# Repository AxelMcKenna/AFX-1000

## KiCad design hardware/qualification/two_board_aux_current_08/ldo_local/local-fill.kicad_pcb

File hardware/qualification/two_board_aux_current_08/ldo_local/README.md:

# Isolated main-LDO local bypass

Final candidate: `inputs-local-return-08/power_protection.kicad_pcb`. Its complete materialized schematic, footprint libraries and project context are frozen under this unique run directory and bound by `inputs-local-return-08.json`. This is not selected TBP73 and does not complete IN/EN source delivery or the held-rail design.

P_C907 is KEMET C0603C105K3RACTU, nominal 1 µF / 25 V X7R / 10%, at (187.5,126.6), F.Cu, 180°. Its positive pad connects to P_U102.8 through 0.809217 mm of 0.3 mm trace; its ground pad connects directly to P_U102.9 through 3.383580 mm of 0.4 mm trace. Four surface tracks, no vias, no existing part moved. The earlier 2.779 mm lead followed by 13.019 mm of existing ground chain is rejected as a short local bypass path.

The In1 main-ground patch is the explicit rectangle (186.7,127.8)–(188.0,130.8), 3.9 mm². Native fill contact is anchored to two original main-ground zones with 16 and four source-connected contacts respectively. All original native groups, quiet objects, copper and 55 full-identity anonymous pad mappings are preserved except the declared two new capacitor joins; opens remain 1,943. All original pads/tracks retain their reference copper, and new copper and conservative new pad rectangles clear both mechanical keepout sets.

The F.Cu AGND cutback is explicitly local, not a clearance waiver: source zone `d0572a8e-b95d-5c59-9a7c-1d3514a507b4`, first native corner-run replace 118:138 with 118:132. It removes 0.744739497 mm² within (187.69,125.95)–(188.57,127.65), adds none, preserves every old ground contact and leaves the other 48 source zones exact. Its thin native peninsula next to an old DC_IN antipad extends beyond a simple pad-clearance offset; the exact saved native corner-run and bounded rectangle are the review authority. Remote refill runs and the extra native polygon are rejected. Clearance rules are unchanged.

The selected-zone native interface loads/checks the whole board, builds connectivity, fills only the new zone, then imports only that fill. `failure-provenance.json` retains the prior 180 s full-board CLI timeout and the successful 2.16 s changed-workload diagnostic. The timeout's internal cause is not established. No unchanged failed operation was retried. `native-07` additionally had a new reference-text overlap; the final candidate changes only C907 reference size/position and checks exact board AST equality otherwise.

Schematic UUID and footprint identity are checked separately from net parity, including all 1,105 electrical parts and C907. Native command completion alone never passes the gate: the host manifest must match every native input byte, and recorded process hashes must match expected host hashes even when `inputs_unchanged` is true. This addresses the rejected `native-06` reused-path discrepancy without modifying a shared runner.

Qualification remains conditional. TI's hard input-capacitance minimum is effective 0.1 µF; the long-source 10 µF recommendation is not satisfied by assuming nominal 1 µF. The cached KEMET primary PDF page 2 bias curves are typical simulations, explicitly not specifications on page 4. Actual effective capacitance over voltage/temperature/age, the 39.247 mm input feed and existing remote C102 transient behavior, installed current/thermal performance, IN/EN routing and the wider reset/held-distribution gates remain open. Maximum capacitor body height is 0.95 mm; housing integration has not been qualified. Four TPS3703 DSE 0.15 mm clearances remain unwaived against the 0.20 mm rule.

Run the verifier and ten mutation tests:

```
.venv/bin/python -m hardware.qualification.two_board_aux_current_08.ldo_local.verify
.venv/bin/python -m unittest hardware.qualification.two_board_aux_current_08.ldo_local.test_verify
```

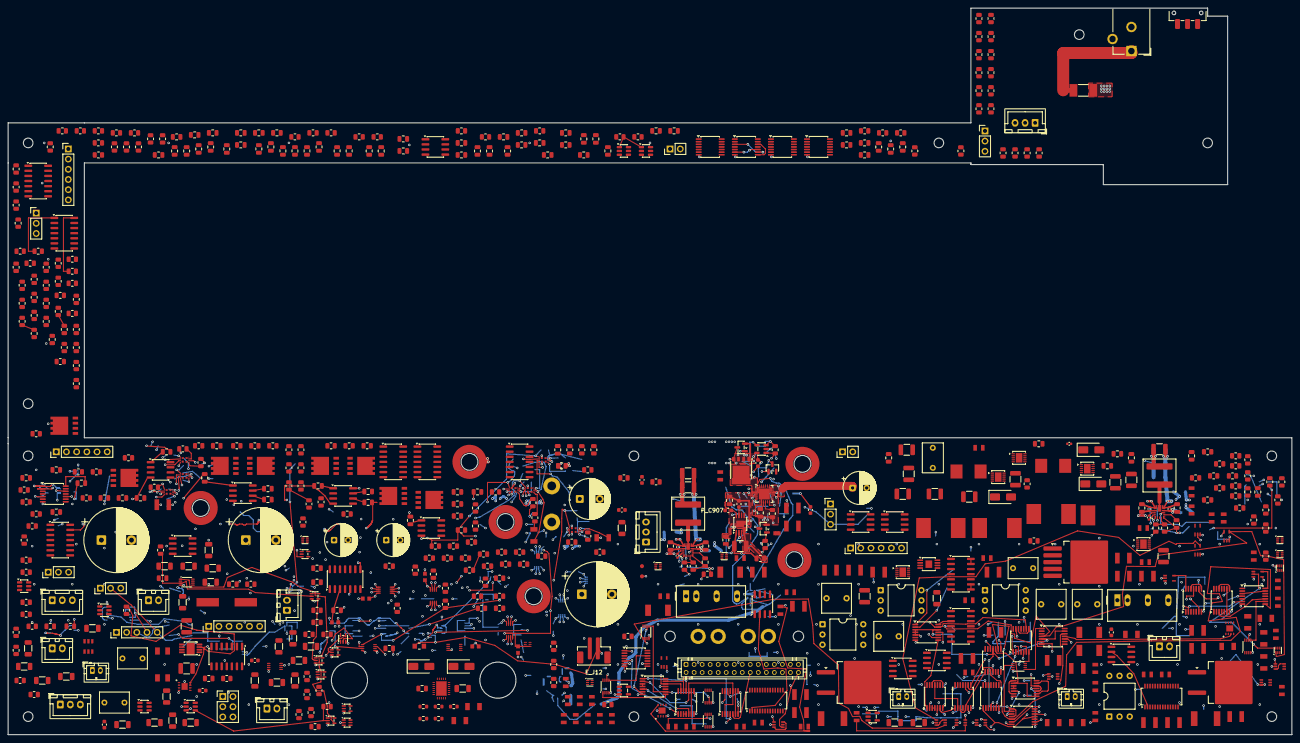
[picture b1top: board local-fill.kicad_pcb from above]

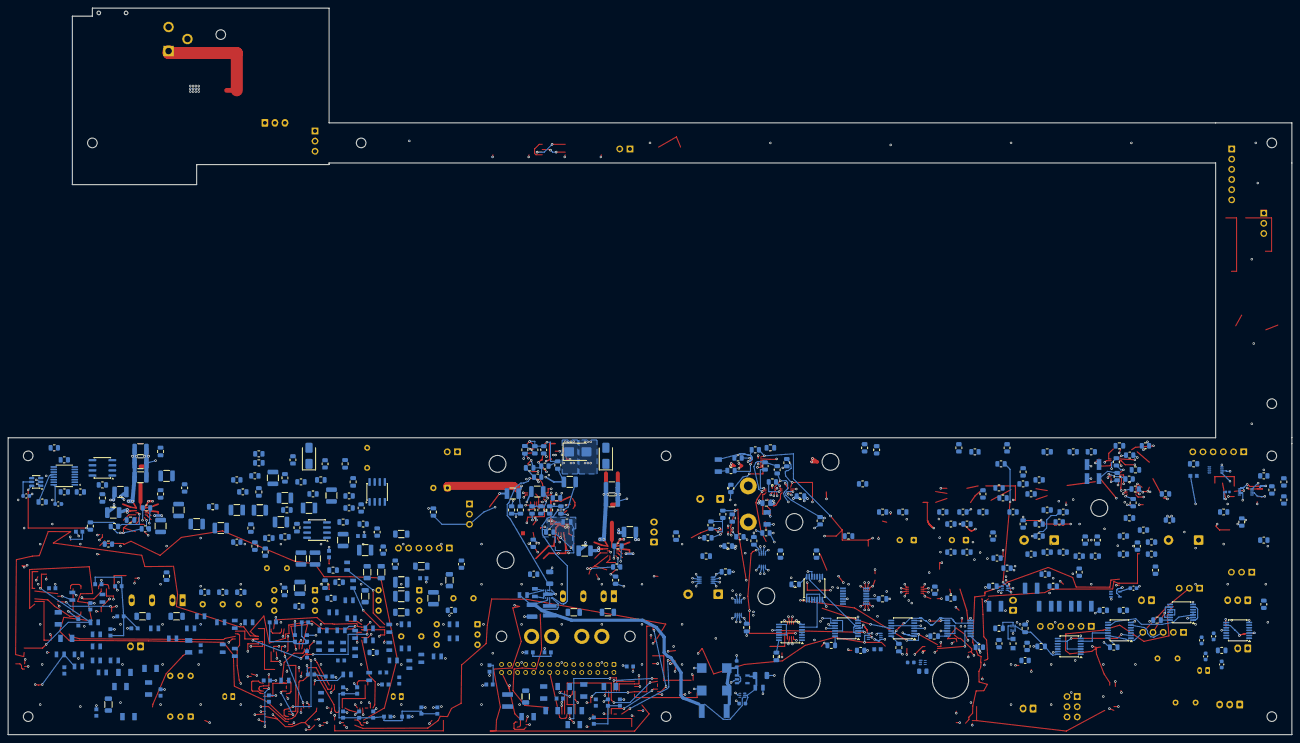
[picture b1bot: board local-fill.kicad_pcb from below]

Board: 8 copper layers, 320.0 x 181.1 mm, 1120 parts (428 on the bottom side), 643 nets.

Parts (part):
E_C1, E_C5, E_C17, E_C21, E_C25, E_C34, E_C35, E_C37, E_C57, E_C58, E_C59, E_C66, E_C67, E_C68, E_C69, E_C70, E_C71, E_C72, E_C73, E_C74, E_C75, E_C76, E_C77: 100nF 16V X7R; C_0805_2012Metric
E_C2, E_C3, E_C6, E_C7, E_C10, E_C11, E_C14, E_C15: 10pF 100V C0G 5%; C_0805_2012Metric
E_C4, E_C8: 1500uF 35V electrolytic 20% EEUFR1V152S; CP_Radial_D16.0mm_P7.50mm
E_C9, E_C13, E_C29, E_C36: 100nF 50V X7R 10%; C_0805_2012Metric
E_C12, E_C16: 220uF 35V electrolytic 20% EEUFR1V221; CP_Radial_D8.0mm_P3.50mm
E_C20: 1500uF 16V electrolytic 20% EEUFR1C152; CP_Radial_D10.0mm_P5.00mm
E_C24: 4700uF 16V electrolytic 20% EEUFR1C472; CP_Radial_D16.0mm_P7.50mm
E_C26: 1uF 16V X7R; C_0805_2012Metric
E_C27, E_C28, E_C30, E_C31, E_C32, E_C33, E_C53, E_C54, E_C55, E_C56: 100pF 50V C0G 5%; C_0805_2012Metric
E_C38: 10uF 16V X7R; C_0805_2012Metric
E_C39, E_C41, E_C49, E_C61, E_C62, E_C63, E_C64, E_C65: 100nF 50V C0G 5% C1210C104J5GACTU; KEMET_C1210_LevelB
E_C40, E_C42, E_C44, E_C46, E_C48, E_C50, E_C52: 1uF 50V X7R; C_0805_2012Metric
E_C43, E_C45, E_C47, E_C51: 47nF 50V C0G 5% C1206C473J5GACTU; KEMET_C1206_LevelB
E_C60: 10nF 50V C0G 5%; C_0805_2012Metric
E_C78, E_C80, E_C81, E_C82, E_C83, E_C84, E_C85: 100nF 16V X7R 10% KEMET C0603C104K4RACTU; KEMET_C0603_LevelB
E_C79: 100nF 16V X7R 10% KEMET C0402C104K4RACTU; KEMET_C0402_LevelB
E_C86: 100nF 50V X7R C0603C104K5RACTU; AX03_C0603
E_C900: 100nF 50V X7R 10%; TB05_P_Capacitor_SMD__C_0603_1608Metric
E_J1, E_J3: Header6; PinHeader_1x06_P2.54mm_Vertical
E_J4: Alpha3079_AWG14_DIG_FORCE; AWG14_Force_2x1_P9mm_Engineering
E_J5, E_J6: Header3; PinHeader_1x03_P2.54mm_Vertical
E_J7, E_J8, E_J10, E_J11: 7466003R; 7466003R_M3_SMT_Annulus_NPTH
E_J9: E28 CONTROL; PinHeader_1x05_P2.54mm_Vertical
E_J12: JST B2B-PH-SM4-TB(LF)(SN); JST_B2B_PH_SM4_TB_MechanicalLands
E_Q1, E_Q2, E_Q3, E_Q4, E_Q5, E_Q6, E_Q7, E_Q8: CSD18540Q5B; CSD18540Q5B_TI_Q5B
E_R1, E_R9, E_R17, E_R25: 22 1%; R_0805_2012Metric
E_R2, E_R10, E_R18, E_R26, E_R60, E_R63, E_R68, E_R71, E_R76, E_R81, E_R86, E_R91: 20M 1%; R_0805_2012Metric
E_R3, E_R5, E_R11, E_R13, E_R19, E_R21, E_R27, E_R29, E_R61, E_R64, E_R69, E_R72, E_R77, E_R82, E_R87, E_R92: 10k 1%; R_0805_2012Metric
E_R4, E_R12, E_R20, E_R28, E_R98, E_R102, E_R106, E_R110, E_R114, E_R118, E_R122: 100 1%; R_0805_2012Metric
E_R6, E_R7, E_R14, E_R15, E_R22, E_R23, E_R30, E_R31: 15k 1%; R_0805_2012Metric
E_R8, E_R16, E_R24, E_R32, E_R40, E_R48: 47k 1%; R_0805_2012Metric
E_R49: 150k 0.01% 5ppm; R_0805_2012Metric
E_R50: 6.2k 0.01% 5ppm; R_0805_2012Metric
E_R51, E_R54, E_R58, E_R59, E_R62, E_R66, E_R67, E_R70, E_R74, E_R75, E_R79, E_R80, E_R85, E_R90, E_R94, E_R124, E_R127, E_R130, E_R133: 10k 0.01% 5ppm; R_0805_2012Metric
E_R52, E_R55: 1k 1%; R_0805_2012Metric
E_R53: 100k 0.01% 5ppm; R_0805_2012Metric
E_R56: 143k 0.01% 5ppm; R_0805_2012Metric
E_R57: 3.3k 0.01% 5ppm; R_0805_2012Metric
E_R65: 90.9k 0.01% 5ppm; R_0805_2012Metric
E_R73, E_R78: 31.6k 0.01% 5ppm; R_0805_2012Metric
E_R83: 10.7k 0.01% 5ppm; R_0805_2012Metric
E_R84: 5.76k 0.01% 5ppm; R_0805_2012Metric
E_R88: 16.2k 0.01% 5ppm; R_0805_2012Metric
E_R89: 13.3k 0.01% 5ppm; R_0805_2012Metric
E_R93: 200k 0.1% ERA6AEB204V - COMPLETE1% RECEIVING; R_0805_2012Metric
E_R95, E_R99, E_R103, E_R107, E_R111, E_R115, E_R119, E_R125, E_R128, E_R131, E_R134, E_R136, E_R141: 10k; R_0805_2012Metric
E_R96, E_R100, E_R104, E_R108, E_R112, E_R116, E_R120, E_R140: 47k; R_0805_2012Metric
E_R97, E_R101, E_R117: 2.43k 0.1%; R_0805_2012Metric
E_R105, E_R109, E_R113, E_R121: 604 0.1%; R_0805_2012Metric
E_R123, E_R126, E_R129, E_R132: 28.7k 0.01% 5ppm; R_0805_2012Metric
E_R135: 10k 0.1% 25ppm Panasonic ERA6AEB103V; Resistor_SMD_Panasonic_ERA6A_2012
E_R137: 11.1k 0.1%; R_0805_2012Metric
E_R138: 39.2 0.1%; R_0805_2012Metric
E_R139: 10k 0.1%; R_0805_2012Metric
E_R142: 15k; R_0805_2012Metric
E_R143: 15k 0.1% 25ppm Panasonic ERA6AEB153V; Resistor_SMD_Panasonic_ERA6A_2012
E_R900: 10k 0.1% 25ppm; TB05_E_Resistor_SMD__R_0805_2012Metric
E_U1, E_U2, E_U3, E_U4: SI8751AB-ISR; SOIC-8_3.9x4.9mm_P1.27mm
E_U7: REF35125QDBVR; SOT-23-6
E_U8: OPA2333AID; SOIC-8_3.9x4.9mm_P1.27mm
E_U9, E_U10: TLV1824DR; SOIC-14_3.9x8.7mm_P1.27mm
E_U11, E_U12, E_U24, E_U25, E_U26, E_U27: SN74LVC08APWR; TSSOP-14_4.4x5mm_P0.65mm
E_U13, E_U14, E_U15, E_U16, E_U17, E_U32, E_U33: TPS259482LYWP; TPS259482L_YWP0012A
E_U18: TLV1824PWR; TLV1824_PW0014A
E_U19, E_U20: TPS389001DSET; TPS389001_DSE0006A
E_U21, E_U22: SN74LVC02APWR; TSSOP-14_4.4x5mm_P0.65mm
E_U23: SN74LVC32APWR; TSSOP-14_4.4x5mm_P0.65mm
E_U28: SN74LVC14APWR; SN74LVC14A_PW0014A
E_U29, E_U30, E_U31, E_U34: SN74AUP2G08DCUR; SN74AUP2G08_DCU0008A
E_U35, E_U36, E_U37, E_U38, E_U39, E_U40, E_U41: SN74AUP3G17DCUR; SN74LVC3G17_DCU0008A
E_U42: SN74LVC3G17DCUR; SN74LVC3G17_DCU0008A
E_U43: SN74AUP1G17DCKR; AX03_DCK0005A
E_U900: TPS3703A5330DSER; AUX_READY__TI_DSE0006A
F_C1, F_C2: 10uF 25V C3225X7R1E106K250AC; Capacitor_SMD__C_1210_3225Metric
F_C3, F_C14, F_C22, F_C23: 10nF 50V C0G C1206C103J5GACTU; Capacitor_SMD__C_1206_3216Metric
F_C4, F_C5, F_C6, F_C8, F_C9, F_C10, F_C11, F_C12, F_C13, F_C15, F_C16, F_C17, F_C18, F_C19, F_C24: 100nF 25V C0G C1206C104J3GACTU; Capacitor_SMD__C_1206_3216Metric
F_C7: 2.7nF 50V C0G5% C0603C272J5GACTU; Capacitor_SMD__C_0603_1608Metric
F_C20, F_C21: 15pF 50V C0G5% C0603C150J5GACTU; Capacitor_SMD__C_0603_1608Metric
F_C201, F_C202, F_C301, F_C302: 100nF25V C0G5% C1206C104J3GACTU; Capacitor_SMD__C_1206_3216Metric
F_C203, F_C303: 1uF63V10% WIMA MKS2C041001F00KSSD; Capacitor_THT__C_Rect_L7.2mm_W5.0mm_P5.00mm
F_C401, F_C402, F_C403, F_C404: 100nF50V X7R10% C0603C104K5RACTU - EFFECTIVE60nF_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; Capacitor_SMD__C_0603_1608Metric
F_J2, F_J3, F_J4, F_J201: JST B2B-XH-A / XHP-2 / SXH-001T-P0.6; Connector_JST__JST_XH_B2B-XH-A_1x02_P2.50mm_Vertical
F_J5: AVRISP2x3 target-powered3.3V sense ONLY; Connector_PinHeader_2.54mm__PinHeader_2x03_P2.54mm_Vertical
F_J202, F_J203: JST B3B-XH-A / XHP-3 / SXH-001T-P0.6; Connector_JST__JST_XH_B3B-XH-A_1x03_P2.50mm_Vertical
F_J401: JST B2B-PH-K-S / PHR-2 / SPH-002T-P0.5S; Connector_JST__JST_PH_B2B-PH-K_1x02_P2.00mm_Vertical
F_R1, F_R16, F_R17, F_R21, F_R23: 1k 0.1%25ppm TNPW08051K00BEEA; Resistor_SMD__R_0805_2012Metric
F_R2, F_R6, F_R10, F_R13, F_R202, F_R302: 10k 0.1%25ppm TNPW080510K0BEEA; Resistor_SMD__R_0805_2012Metric
F_R3, F_R4, F_R5, F_R7, F_R14, F_R15: 47k 0.1%25ppm TNPW080547K0BEEA; Resistor_SMD__R_0805_2012Metric
F_R8: 68k 0.1%25ppm TNPW080568K0BEEA; Resistor_SMD__R_0805_2012Metric
F_R9: 39k 0.1%25ppm TNPW080539K0BEEA; Resistor_SMD__R_0805_2012Metric
F_R11: 56.2k 0.1%25ppm TNPW080556K2BEEA; Resistor_SMD__R_0805_2012Metric
F_R12, F_R24, F_R201, F_R203, F_R301, F_R303: 100k 0.1%25ppm TNPW0805100KBEEA; Resistor_SMD__R_0805_2012Metric
F_R20, F_R22: 20k 0.1%25ppm TNPW080520K0BEEA; Resistor_SMD__R_0805_2012Metric
F_R401: 220k 0.1%25ppm TNPW0805220KBEEA - COMPLETE1% RECE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; Resistor_SMD__R_0805_2012Metric
F_U1: ATtiny84A-SSUR; Package_SO__SOIC-14_3.9x8.7mm_P1.27mm
F_U2: TPS7A1633DGNR; TI_DGN0008C
F_U3: SN74LVC2G17DCKR; Package_TO_SOT_SMD__SOT-363_SC-70-6
F_U4: TPS3431SDRBR; TI_DRB0008A_TPS3431
F_U5: SN74AUP1G17DCKR; Package_TO_SOT_SMD__SOT-353_SC-70-5
F_U6: SN74LVC1T45DBVR; Package_TO_SOT_SMD__SOT-23-6
F_U7: SN74LVC1G14DCKR; Package_TO_SOT_SMD__SOT-353_SC-70-5
F_U8: SN74LVC1G74DCUR; TI_DCU0008A
F_U9: TPS389001DSET; Package_SON__WSON-6_1.5x1.5mm_P0.5mm
F_U10, F_U11: SN74LVC1G17DCKR; Package_TO_SOT_SMD__SOT-353_SC-70-5
F_U12, F_U13: SN74LVC1G08DCKR; Package_TO_SOT_SMD__SOT-353_SC-70-5
F_U14: SN74LVC1G06DCKR; Package_TO_SOT_SMD__SOT-353_SC-70-5
F_U15: TLP175A(TPL,E); RMX_FH02__TLP175A_11-4M1S_Receiving
F_U16: SN74LVC1G34DCKR; Package_TO_SOT_SMD__SOT-353_SC-70-5
F_U201, F_U301: TPS2553DBVR-1; Package_TO_SOT_SMD__SOT-23-6
F_U401: TPS2553DBVR-1; TI_DBV0006A
F_X1: ABLS-4.000MHZ-12-D4Y-T; RMX_FH02__ABLS_Manufacturer_Land
G_C1: 1uF 50V X7R 10%; C_0805_2012Metric
G_C2: 2.2uF 50V X7R 10%; C_1206_3216Metric
G_C3, G_C4: 100nF25V C0G C1206C104J3GACTU; PROPOSED_KEMET1206_LevelB
G_D1: SMAJ15A-E3/61; D_SMA
G_D2: SS14-E3/61T; D_SMA
G_NT1: MODULE_RETURN_STAR; Return_Star
G_R1, G_R3: 470k 0.1% 25ppm; R_0603_1608Metric
G_R2: 59.0k 0.1% 25ppm; R_0603_1608Metric
G_R4: 43.2k 0.1% 25ppm; R_0603_1608Metric
G_R5: 22.1k 0.1% 25ppm; R_0603_1608Metric
G_U1: TPS26601RHFR; TI_RHF0024A
H_NEW1: PROPOSED_NPTH; H_NEW1
H_NEW2: PROPOSED_NPTH; H_NEW2
H_NEW3: PROPOSED_NPTH; H_NEW3
H_NEW4: PROPOSED_NPTH; H_NEW4
H_NEW5: PROPOSED_NPTH; H_NEW5
H_NEW6: PROPOSED_NPTH; H_NEW6
H_NEW7: PROPOSED_NPTH; H_NEW7
H_NEW8: PROPOSED_NPTH; H_NEW8
H_NEW9: PROPOSED_NPTH; H_NEW9
H_NEW10: PROPOSED_NPTH; H_NEW10
H_NEW11: PROPOSED_NPTH; H_NEW11
H_TOUCH1: PROPOSED_NPTH; H_TOUCH1
H_TOUCH2: PROPOSED_NPTH; H_TOUCH2
I_F1: 045106.3MRL 6.3A 125V; Fuse_Littelfuse-NANO2-451_453
I_J1: PJ-102AH; PJ102AH_RearEdge_E23
I_J3: B3B-XH-A(LF)(SN); JST_XH_B3B-XH-A_1x03_P2.50mm_Vertical
I_S1: JS102011SAQN; JS102011SAQN_RearEdge_E23
M_C1, M_C2, M_C3, M_C4, M_C5, M_C6, M_C7, M_C8, M_C9, M_C10, M_C11, M_C12, M_C13, M_C14, M_C15, M_C16, M_C17, M_C18, M_C19, M_C20, M_C21, M_C22, M_C23, M_C24, M_C25, M_C26, M_C27, M_C28, M_C29, M_C30, M_C31, M_C32, M_C33, M_C34, M_C35, M_C36: 100pF C0G 5%; C_0805_2012Metric
M_C37, M_C38, M_C39, M_C40, M_C41, M_C42, M_C43, M_C44, M_C45, M_C46, M_C47, M_C48: 100nF 16V X7R; C_0805_2012Metric
M_C49: 2.2uF 16V X7R; C_0805_2012Metric
M_C50: 10uF 16V X7R; C_0805_2012Metric
M_C51: 1uF 16V X7R; C_0805_2012Metric
M_J1, M_J3: Conn_01x03; PinHeader_1x03_P2.54mm_Vertical
M_J2: Conn_01x06; PinHeader_1x06_P2.54mm_Vertical
M_J4: Conn_01x02; PinHeader_1x02_P2.54mm_Vertical
M_R1, M_R7, M_R25, M_R31: 91k 0.01% 5ppm; R_0805_2012Metric
M_R2, M_R4, M_R8, M_R10, M_R11, M_R14, M_R16, M_R19, M_R21, M_R22, M_R26, M_R28, M_R32, M_R33, M_R35, M_R36, M_R39, M_R41, M_R44, M_R45, M_R47, M_R48, M_R51, M_R53, M_R56, M_R58, M_R59, M_R62, M_R64, M_R67, M_R69, M_R70, M_R73, M_R75, M_R77, M_R80, M_R82, M_R84, M_R85, M_R88, M_R90, M_R92, M_R96, M_R98, M_R99, M_R103, M_R105, M_R106, M_R108, M_R111: 10k 0.01% 5ppm; R_0805_2012Metric
M_R3: 3.57k 0.01% 5ppm; R_0805_2012Metric
M_R5, M_R12, M_R17, M_R23, M_R29, M_R37, M_R42, M_R49, M_R54, M_R60, M_R65, M_R71, M_R78, M_R86, M_R93, M_R100: 20M 1%; R_0805_2012Metric
M_R6, M_R13, M_R18, M_R24, M_R30, M_R38, M_R43, M_R50, M_R55, M_R61, M_R66, M_R72, M_R79, M_R87, M_R94, M_R101, M_R113: 10k 1%; R_0805_2012Metric
M_R9: 3.01k 0.01% 5ppm; R_0805_2012Metric
M_R15: 3.4k 0.01% 5ppm; R_0805_2012Metric
M_R20: 2.87k 0.01% 5ppm; R_0805_2012Metric
M_R27, M_R95: 11.5k 0.01% 5ppm; R_0805_2012Metric
M_R34: 604 0.01% 5ppm; R_0805_2012Metric
M_R40: 11.3k 0.01% 5ppm; R_0805_2012Metric
M_R46: 412 0.01% 5ppm; R_0805_2012Metric
M_R52, M_R63: 8.2k 0.01% 5ppm; R_0805_2012Metric
M_R57, M_R68: 1.78k 0.01% 5ppm; R_0805_2012Metric
M_R74, M_R81, M_R89: 499 0.01% 5ppm; R_0805_2012Metric
M_R76: 374 0.01% 5ppm; R_0805_2012Metric
M_R83: 127 0.01% 5ppm; R_0805_2012Metric
M_R91: 768 0.01% 5ppm; R_0805_2012Metric
M_R97: 270 0.01% 5ppm; R_0805_2012Metric
M_R102, M_R104: 100k 0.01% 5ppm; R_0805_2012Metric
M_R107, M_R109: 80.6k 0.01% 5ppm; R_0805_2012Metric
M_R110: 105k 0.01% 5ppm; R_0805_2012Metric
M_R112: 100k 1%; R_0805_2012Metric
M_R114: 330k 1%; R_0805_2012Metric
M_U1, M_U2, M_U3, M_U4: TLV1824IDR; SOIC-14_3.9x8.7mm_P1.27mm
M_U5: OPA4192ID; SOIC-14_3.9x8.7mm_P1.27mm
M_U6: REF5025EIDR; SOIC-8_3.9x4.9mm_P1.27mm
M_U7: TPS3808G01DBVR; SOT-23-6
M_U8: TPS3808G33DBVR; SOT-23-6
M_U9, M_U10, M_U11, M_U12: SN74LVC08APWR; TSSOP-14_4.4x5mm_P0.65mm
N_C1: 56nF50V C0G5% C1206C563J5GACTU - COMPLETE10% RECE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; PROPOSED_KEMET1206_LevelB
N_C2: 33nF50V C0G5% C1206C333J5GACTU - COMPLETE10% RECE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; PROPOSED_KEMET1206_LevelB
N_C3, N_C12, N_C39, N_C55, N_C56, N_C57, N_C58, N_C59, N_C60, N_C61, N_C62, N_C63, N_C64, N_C65, N_C66, N_C67, N_C68, N_C69, N_C70, N_C71, N_C72, N_C73, N_C74, N_C75, N_C76, N_C77, N_C78, N_C79, N_C80, N_C81, N_C82, N_C83, N_C84, N_C85, N_C86, N_C87, N_C88: 100nF 50V X7R10% C0603C104K5RACTU - bypass effect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; PROPOSED_KEMET0603_LevelB
N_C4, N_C31: 10uF 25V X7R MODULE INPUT FILTER/EFFECTIVE/INRUSH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; Capacitor_SMD__C_1206_3216Metric
N_C5, N_C32: 1uF 50V X7R MODULE OUTPUT FILTER/EFFECTIVE HOLD; Capacitor_SMD__C_1206_3216Metric
N_C6, N_C33: 1uF 25V X7R LTC4261 local VIN effective HOLD; Capacitor_SMD__C_1206_3216Metric
N_C7, N_C9, N_C11, N_C13, N_C34, N_C36, N_C38, N_C40: 100nF 25V C0G C1206C104J3GACTU; PROPOSED_KEMET1206_LevelB
N_C8, N_C10, N_C35, N_C37: 10nF 50V C0G COMPLETE10% TIMING RECEIVING; PROPOSED_KEMET1206_LevelB
N_C14, N_C15, N_C16, N_C17, N_C18, N_C19, N_C20, N_C21, N_C22, N_C23, N_C24, N_C25, N_C41, N_C42, N_C43, N_C44, N_C45, N_C46, N_C47, N_C48, N_C49: 100nF 50V C0G C1210C104J5GACTU - COMPLETE10% RAMP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; PROPOSED_KEMET1210_LevelB
N_C26, N_C27, N_C50, N_C51: 2.2uF 63V PET5% MKS2C042201K00JSSD - COMPLETE10% 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; Capacitor_THT__C_Rect_L7.2mm_W7.2mm_P5.00mm_FKS2_FKP2_MKS2_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
N_C28, N_C30, N_C52, N_C54: 47nF 50V C0G C1206C473J5GACTU; PROPOSED_KEMET1206_LevelB
N_C29, N_C53: 100nF 50V C0G C1210C104J5GACTU; PROPOSED_KEMET1210_LevelB
N_C89, N_C90, N_C91, N_C93, N_C94, N_C96: 100nF50V X7R10% C0603C104K5RACTU - EFFECTIVE/PDN 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; PROPOSED_KEMET0603_LevelB
N_C92, N_C95: 47nF50V C0G5% C1206C473J5GACTU - COMPLETE6% RECEI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; PROPOSED_KEMET1206_LevelB
N_C97, N_C98: 100nF25V C0G5% C1206C104J3GACTU - COMPLETE6% CT /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; PROPOSED_KEMET1206_LevelB
N_C99: 100nF25V C0G5% C1206C104J3GACTU - COMPLETE6% UVRE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; PROPOSED_KEMET1206_LevelB
N_C100: 100nF50V X7R10% C0603C104K5RACTU - LOCAL_BYPASS_E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; PROPOSED_KEMET0603_LevelB
N_H101, N_H102: STRAIN_POST_2p6_NPTH_RECEIVING
N_J1: NEW NF03C CONTROL/KELVIN INTERFACE - physical con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; NC265_JST_PHD_B30B-PHDSS_2x15_P2.00mm_Vertical
N_J2: N19 NEW FORCE IN/OUT - connector and harness unse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; NC265_NC265_Force2_18AWG_P5_Drill2p2_Land3p8
N_J3: N19 E28 BANK GATE/COMMON CLAMP - physical interfa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; NC265_JST_PH_B2B-PH-K_1x02_P2.00mm_Vertical
N_J4: N12 NEW FORCE IN/OUT - connector and harness unse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; NC265_NC265_Force2_18AWG_P5_Drill2p2_Land3p8
N_J5: N12 E28 BANK GATE/COMMON CLAMP - physical interfa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; NC265_JST_PH_B2B-PH-K_1x02_P2.00mm_Vertical
N_J6: NEW MODULE INPUT ONLY - keyed JST XH2 receiving c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; NC265_JST_XH_B2B-XH-A_1x02_P2.50mm_Vertical
N_Q1, N_Q2: CSD19536KTT; Package_TO_SOT_SMD__TO-263-2
N_R1, N_R2, N_R8, N_R9: 10k; PROPOSED_TNPW0805_IPC28950
N_R3, N_R10: 205000ohm 0.1% TNPW0805205KBEEA - COMPLETE3% RECE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; PROPOSED_TNPW0805_IPC28950
N_R4, N_R11: 499ohm 0.1% TNPW0805499RBEEA - COMPLETE3% RECEIVI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; PROPOSED_TNPW0805_IPC28950
N_R5, N_R12, N_R95, N_R98, N_R99: 10000ohm 0.1% TNPW080510K0BEEA - COMPLETE3% RECEI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; PROPOSED_TNPW0805_IPC28950
N_R6, N_R7, N_R13, N_R14: 220ohm COMPLETE +/-3% RECEIVING; PROPOSED_TNPW0805_IPC28950
N_R15, N_R16, N_R17, N_R18, N_R19, N_R20, N_R21, N_R22: 47k 3% TOTAL RECEIVING; PROPOSED_TNPW0805_IPC28950
N_R23: 160000ohm COMPLETE0.1% RECEIVING; PROPOSED_TNPU0805_IPC28950
N_R24, N_R41, N_R63, N_R65, N_R80, N_R82: 10k COMPLETE0.1% RECEIVING; PROPOSED_TNPU0805_IPC28950
N_R25, N_R49: 8660ohm COMPLETE0.1% RECEIVING; PROPOSED_TNPU0805_IPC28950
N_R26, N_R50: 35.7ohm COMPLETE0.1% RECEIVING; PROPOSED_TNPU0603_IPC28950
N_R27, N_R31, N_R35, N_R44, N_R47, N_R51: 100k COMPLETE0.1% RECEIVING; PROPOSED_TNPU0805_IPC28950
N_R28, N_R32, N_R36, N_R37, N_R38, N_R39, N_R45, N_R48, N_R52, N_R53, N_R54, N_R55, N_R59, N_R76: 10k COMPLETE3% RECEIVING; PROPOSED_TNPW0805_IPC28950
N_R29, N_R46: 2000ohm COMPLETE0.1% RECEIVING; PROPOSED_TNPU0805_IPC28950
N_R30: 40.2ohm COMPLETE0.1% RECEIVING; PROPOSED_TNPU0603_IPC28950
N_R33: 6040ohm COMPLETE0.1% RECEIVING; PROPOSED_TNPU0805_IPC28950
N_R34: 75ohm COMPLETE0.1% RECEIVING; PROPOSED_TNPU0603_IPC28950
N_R40: 102000ohm COMPLETE0.1% RECEIVING; PROPOSED_TNPU0805_IPC28950
N_R42: 10700ohm COMPLETE0.1% RECEIVING; PROPOSED_TNPU0805_IPC28950
N_R43: 169ohm COMPLETE0.1% RECEIVING; PROPOSED_TNPU0805_IPC28950
N_R56, N_R57, N_R73, N_R74: 402ohm 1% CRCW2010402RFKEF - COMPLETE3% RECEIVING; PROPOSED_CRCW2010_reflow20035
N_R58, N_R60, N_R61, N_R66, N_R67, N_R68, N_R75, N_R77, N_R78, N_R83, N_R84, N_R85: 47k COMPLETE3% RECEIVING; PROPOSED_TNPW0805_IPC28950
N_R62, N_R79: 30.4k COMPLETE0.1% RECEIVING; PROPOSED_TNPU0805_IPC28950
N_R64, N_R81: 78.7k COMPLETE0.1% RECEIVING; PROPOSED_TNPU0805_IPC28950
N_R69: 0.33ohm COMPLETE5% SHUNT RECEIVING; PROPOSED_WSL2512_7m_to500m
N_R70, N_R87: 10ohm COMPLETE3% RECEIVING; PROPOSED_TNPW0805_IPC28950
N_R71, N_R88: 1M; PROPOSED_TNPW0805_IPC28950
N_R72: 27ohm COMPLETE3% RECEIVING; PROPOSED_TNPW0805_IPC28950
N_R86: 0.12ohm COMPLETE5% SHUNT RECEIVING; PROPOSED_WSL2512_7m_to500m
N_R89: 39ohm COMPLETE3% RECEIVING; PROPOSED_TNPW0805_IPC28950
N_R90, N_R91: 10k0.1% TNPW080510K0BEEA - COMPLETE3% RECEIVING; PROPOSED_TNPW0805_IPC28950
N_R92: 11300ohm 0.02% 2ppm TNPU080511K3HWEN00 - COMPLETE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; PROPOSED_TNPW0805_IPC28950
N_R93: 49.9ohm 0.1% TNPW080549R9BEEA - COMPLETE0.7% TRIM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; PROPOSED_TNPW0805_IPC28950
N_R94: 10000ohm 0.02% 2ppm TNPU080510K0HWEN00 - COMPLETE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; PROPOSED_TNPW0805_IPC28950
N_R96: 47000ohm 0.1% TNPW080547K0BEEA - COMPLETE3% RECEI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; PROPOSED_TNPW0805_IPC28950
N_R97: 680ohm 0.1% TNPW1206680RBEEA - COMPLETE3% RECEIVI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; PROPOSED_TNPW1206_IPC28950
N_U1, N_U2, N_U7, N_U8: SN74AUP1G74DCUR; NF05R_Manufacturer__TI_DCU0008A
N_U3, N_U9: TPS3431SDRBR; TI_DRB0008A_TPS3431
N_U4, N_U10: SN74LVC1G06DBVR; Package_TO_SOT_SMD__SOT-23-5
N_U5, N_U6, N_U11, N_U12: TLP4590AF(F; Package_DIP__DIP-6_W10.16mm
N_U13: OPA2333AID; Package_SO__SOIC-8_3.9x4.9mm_P1.27mm
N_U14: TLV1822DR; Package_SO__SOIC-8_3.9x4.9mm_P1.27mm
N_U15: TLV1824DR; Package_SO__SOIC-14_3.9x8.7mm_P1.27mm
N_U16, N_U27: SN74LVC2T45DCUR; NF05R_Manufacturer__TI_DCU0008A
N_U17, N_U22: TMR 1-1215; Converter_DCDC__Converter_DCDC_TRACO_TMR-1-xxxx_Single_THT
N_U18, N_U23: LTC4261IGN#PBF; Package_SO__SSOP-28_3.9x9.9mm_P0.635mm
N_U19, N_U24: ISO7721FDR; Package_SO__SOIC-8_3.9x4.9mm_P1.27mm
N_U20, N_U21, N_U25, N_U26, N_U52, N_U54, N_U56: TPS389001DSET; Package_SON__WSON-6_1.5x1.5mm_P0.5mm
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
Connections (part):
/E_rail_disconnect/5V_DIG_OV_OK: E_R81.1, E_R82.2, E_U10.1, E_U37.6
/E_rail_disconnect/5V_DIG_OV_OK_SCHMITT: E_U11.10, E_U37.2
/E_rail_disconnect/5V_DIG_OV_REF: E_R80.2, E_R81.2, E_U10.7
/E_rail_disconnect/5V_DIG_OV_SENSE: E_C33.1, E_R78.2, E_R79.1, E_U10.6
/E_rail_disconnect/ANA_OUTPUT_OK: E_R131.2, E_U18.14, E_U39.3
/E_rail_disconnect/ANA_OUTPUT_OK_SCHMITT: E_U24.4, E_U39.5
/E_rail_disconnect/ANA_PG0: E_R95.1, E_U13.3, E_U41.3
/E_rail_disconnect/ANA_PG0_SCHMITT: E_U31.2, E_U41.5
/E_rail_disconnect/ANA_PG1: E_R99.1, E_U14.3, E_U41.6
/E_rail_disconnect/ANA_PG1_SCHMITT: E_U34.6, E_U41.2
/E_rail_disconnect/ANA_PG2: E_R115.1, E_U32.3, E_U42.1
/E_rail_disconnect/ANA_PG2_SCHMITT: E_U26.10, E_U42.7
/E_rail_disconnect/ANA_SOURCE_OK: E_R125.2, E_U18.2, E_U38.6
/E_rail_disconnect/ANA_SOURCE_OK_SCHMITT: E_U24.1, E_U38.2
/E_rail_disconnect/DIG_OUTPUT_OK: E_R134.2, E_U18.13, E_U39.6
/E_rail_disconnect/DIG_OUTPUT_OK_SCHMITT: E_U24.5, E_U39.2
/E_rail_disconnect/DIG_PG0: E_R103.1, E_U15.3, E_U40.1
/E_rail_disconnect/DIG_PG0_SCHMITT: E_U29.6, E_U40.7
/E_rail_disconnect/DIG_PG1: E_R107.1, E_U16.3, E_U40.3
/E_rail_disconnect/DIG_PG1_SCHMITT: E_U30.2, E_U40.5
/E_rail_disconnect/DIG_PG2: E_R111.1, E_U17.3, E_U40.6
/E_rail_disconnect/DIG_PG2_SCHMITT: E_U34.1, E_U40.2
/E_rail_disconnect/DIG_PG3: E_R119.1, E_U33.3, E_U41.1
/E_rail_disconnect/DIG_PG3_SCHMITT: E_U26.9, E_U30.6, E_U41.7
/E_rail_disconnect/DIG_SOURCE_OK: E_R128.2, E_U18.1, E_U39.1
/E_rail_disconnect/DIG_SOURCE_OK_SCHMITT: E_U24.2, E_U39.7
/E_rail_disconnect/E28_ALL_CHANNELS_READY: E_U26.8, E_U26.12
/E_rail_disconnect/E28_ANA_0_DVDT: E_R98.1, E_U13.7
/E_rail_disconnect/E28_ANA_0_DVDT_CAP: E_C39.1, E_R98.2
/E_rail_disconnect/E28_ANA_0_ILM: E_R97.1, E_U13.9
/E_rail_disconnect/E28_ANA_1_DVDT: E_R102.1, E_U14.7
/E_rail_disconnect/E28_ANA_1_DVDT_CAP: E_C41.1, E_R102.2
/E_rail_disconnect/E28_ANA_1_ILM: E_R101.1, E_U14.9
/E_rail_disconnect/E28_ANA_2_DVDT: E_R118.1, E_U32.7
/E_rail_disconnect/E28_ANA_2_DVDT_CAP: E_C49.1, E_R118.2
/E_rail_disconnect/E28_ANA_2_ILM: E_R117.1, E_U32.9
/E_rail_disconnect/E28_ANA_ENABLE: E_R96.1, E_U13.1, E_U30.3
/E_rail_disconnect/E28_ANA_FOLLOW: E_R100.1, E_U14.1, E_U31.7
/E_rail_disconnect/E28_ANA_FOLLOW2: E_R116.1, E_U32.1, E_U34.3
/E_rail_disconnect/E28_ANA_OUT_SENSE: E_C55.1, E_R129.2, E_R130.1, E_U18.9
/E_rail_disconnect/E28_ANA_SRC_SENSE: E_C53.1, E_R123.2, E_R124.1, E_U18.5
/E_rail_disconnect/E28_ARMED: E_U21.3, E_U21.4, E_U25.9
/E_rail_disconnect/E28_ARM_BAR: E_U21.1, E_U21.6
/E_rail_disconnect/E28_AUX_CT: E_C60.1, E_U19.5
/E_rail_disconnect/E28_AUX_DIV: E_R137.2, E_R138.1
/E_rail_disconnect/E28_AUX_RESET_N: E_U31.5, E_U35.5
/E_rail_disconnect/E28_AUX_RESET_RAW: E_R135.1, E_U19.6, E_U35.3
/E_rail_disconnect/E28_AUX_SENSE: E_R138.2, E_R139.1, E_U19.1
/E_rail_disconnect/E28_DIG_0_DVDT: E_R106.1, E_U15.7
/E_rail_disconnect/E28_DIG_0_DVDT_CAP: E_C43.1, E_R106.2
/E_rail_disconnect/E28_DIG_0_ILM: E_R105.1, E_U15.9
/E_rail_disconnect/E28_DIG_1_DVDT: E_R110.1, E_U16.7
/E_rail_disconnect/E28_DIG_1_DVDT_CAP: E_C45.1, E_R110.2
/E_rail_disconnect/E28_DIG_1_ILM: E_R109.1, E_U16.9
/E_rail_disconnect/E28_DIG_2_DVDT: E_R114.1, E_U17.7
/E_rail_disconnect/E28_DIG_2_DVDT_CAP: E_C47.1, E_R114.2
/E_rail_disconnect/E28_DIG_2_ILM: E_R113.1, E_U17.9
/E_rail_disconnect/E28_DIG_3_DVDT: E_R122.1, E_U33.7
/E_rail_disconnect/E28_DIG_3_DVDT_CAP: E_C51.1, E_R122.2
/E_rail_disconnect/E28_DIG_3_ILM: E_R121.1, E_U33.9
/E_rail_disconnect/E28_DIG_FOLLOW1: E_R108.1, E_U16.1, E_U29.3
/E_rail_disconnect/E28_DIG_FOLLOW2: E_R112.1, E_U17.1, E_U30.7
/E_rail_disconnect/E28_DIG_FOLLOW3: E_R120.1, E_U33.1, E_U34.7
/E_rail_disconnect/E28_DIG_OUT_SENSE: E_C56.1, E_R132.2, E_R133.1, E_U18.11
/E_rail_disconnect/E28_DIG_SRC_SENSE: E_C54.1, E_R126.2, E_R127.1, E_U18.7
/E_rail_disconnect/E28_FAULT: E_J9.4, E_U21.9, E_U21.13, E_U23.5, E_U28.5
/E_rail_disconnect/E28_FAULT_A: E_U23.8, E_U23.12
/E_rail_disconnect/E28_FAULT_ANY: E_U23.11, E_U25.10
/E_rail_disconnect/E28_FAULT_BAR: E_U21.10, E_U21.12
/E_rail_disconnect/E28_MASTER_ENABLE: E_J6.2, E_J9.5, E_R4.1, E_R12.1, E_R20.1, E_R28.1, E_R104.1, E_R141.1, E_U15.1, E_U20.1, E_U20.3, E_U25.13, E_U27.2, E_U29.5, E_U29.7, E_U30.1, E_U30.5, E_U31.1, E_U34.2, E_U34.5
/E_rail_disconnect/E28_NORMAL_OK: E_U22.8, E_U27.8
/E_rail_disconnect/E28_NORMAL_PRE: E_U24.8, E_U27.9
/E_rail_disconnect/E28_NOT_AUX: E_U23.2, E_U28.4
/E_rail_disconnect/E28_NOT_NORMAL_OK: E_U22.10, E_U23.9
/E_rail_disconnect/E28_NOT_OUT_READY: E_U22.13, E_U26.2, E_U26.5
/E_rail_disconnect/E28_NOT_RUN: E_U23.1, E_U28.2, E_U28.9
/E_rail_disconnect/E28_NOT_SOURCE_READY: E_U28.10, E_U28.13
/E_rail_disconnect/E28_OUTPUT_PERMISSION: E_U26.11, E_U27.1
/E_rail_disconnect/E28_OUTPUT_READY: E_J9.3, E_U25.6
/E_rail_disconnect/E28_OUT_ARMED: E_U22.3, E_U22.4, E_U26.1
/E_rail_disconnect/E28_OUT_ARM_BAR: E_U22.1, E_U22.6
/E_rail_disconnect/E28_OUT_READY: E_U22.11, E_U24.6, E_U25.12, E_U26.13
/E_rail_disconnect/E28_OUT_UV_FAULT: E_U23.10, E_U26.3
/E_rail_disconnect/E28_OUT_VALID_ACTIVE: E_U22.2, E_U25.11
/E_rail_disconnect/E28_RESET_OUT: E_U22.5, E_U23.6
/E_rail_disconnect/E28_RUN_AND_SOURCE: E_U24.12, E_U27.6
/E_rail_disconnect/E28_RUN_LOGIC: E_U27.4, E_U28.8
/E_rail_disconnect/E28_SAFE_REQUEST: E_R140.1, E_U12.13, E_U27.11
/E_rail_disconnect/E28_SAFE_STAGE: E_U25.3, E_U27.12
/E_rail_disconnect/E28_SOURCE_READY: E_U24.3, E_U24.9, E_U25.2
/E_rail_disconnect/E28_SOURCE_READY_LOGIC: E_U27.5, E_U27.10, E_U28.12
/E_rail_disconnect/E28_TIMEOUT: E_U26.4, E_U35.7
/E_rail_disconnect/E28_TIMEOUT_CT: E_C61.1, E_C62.1, E_C63.1, E_C64.1, E_C65.1, E_U20.5
/E_rail_disconnect/E28_TIMEOUT_FAULT: E_U23.13, E_U26.6
/E_rail_disconnect/E28_TIMEOUT_RAW: E_R136.1, E_U20.6, E_U35.1
/E_rail_disconnect/E28_USER_AUX: E_U24.11, E_U25.1
/E_rail_disconnect/N12_ALLOW: E_R28.2, E_R29.1, E_U4.3
/E_rail_disconnect/N12_DRIVE: E_R25.1, E_U4.8
/E_rail_disconnect/N12_INV: E_R54.1, E_R55.1, E_U8.7
/E_rail_disconnect/N12_MCAP1: E_C14.2, E_U4.7
/E_rail_disconnect/N12_MCAP1_LIMIT: E_C14.1, E_R30.2
/E_rail_disconnect/N12_MCAP2: E_C15.2, E_U4.6
/E_rail_disconnect/N12_MCAP2_LIMIT: E_C15.1, E_R31.2
/E_rail_disconnect/N12_OV_OK_SCHMITT: E_U11.4, E_U37.7
/E_rail_disconnect/N12_OV_REF: E_R70.2, E_R71.2, E_U9.11
/E_rail_disconnect/N12_SUM: E_R53.2, E_R54.2, E_U8.6
/E_rail_disconnect/N12_TT: E_R27.1, E_U4.2
/E_rail_disconnect/N19_ALLOW: E_R12.2, E_R13.1, E_U2.3
/E_rail_disconnect/N19_DRIVE: E_R9.1, E_U2.8
/E_rail_disconnect/N19_INPUT_MID: E_R49.2, E_R50.1
/E_rail_disconnect/N19_INV: E_R51.1, E_R52.1, E_U8.1
/E_rail_disconnect/N19_MCAP1: E_C6.2, E_U2.7
/E_rail_disconnect/N19_MCAP1_LIMIT: E_C6.1, E_R14.2
/E_rail_disconnect/N19_MCAP2: E_C7.2, E_U2.6
/E_rail_disconnect/N19_MCAP2_LIMIT: E_C7.1, E_R15.2
/E_rail_disconnect/N19_OV_OK_SCHMITT: E_U11.1, E_U36.5
/E_rail_disconnect/N19_OV_REF: E_R62.2, E_R63.2, E_U9.7
/E_rail_disconnect/N19_SUM: E_R50.2, E_R51.2, E_U8.2
/E_rail_disconnect/N19_TT: E_R11.1, E_U2.2
/E_rail_disconnect/NF_VALID_LOGIC: E_U25.5, E_U35.2
/E_rail_disconnect/OK_5: E_U11.8, E_U12.4
/E_rail_disconnect/OK_12: E_U11.6, E_U12.2
/E_rail_disconnect/OK_19: E_U11.3, E_U12.1
/E_rail_disconnect/OK_ALL_OV: E_U12.8, E_U12.12, E_U24.10
/E_rail_disconnect/OK_ANALOG: E_U12.3, E_U12.9
/E_rail_disconnect/OK_AUXILIARY: E_U12.6, E_U12.10
/E_rail_disconnect/OK_REF: E_U11.11, E_U12.5
/E_rail_disconnect/P12_ALLOW: E_R20.2, E_R21.1, E_U3.3
/E_rail_disconnect/P12_COMMON: E_Q5.1, E_Q6.1, E_R18.2, E_U3.5
/E_rail_disconnect/P12_DRIVE: E_R17.1, E_U3.8
/E_rail_disconnect/P12_GATE: E_Q5.2, E_Q6.2, E_R17.2, E_R18.1
/E_rail_disconnect/P12_MCAP1: E_C10.2, E_U3.7
/E_rail_disconnect/P12_MCAP1_LIMIT: E_C10.1, E_R22.2
/E_rail_disconnect/P12_MCAP2: E_C11.2, E_U3.6
/E_rail_disconnect/P12_MCAP2_LIMIT: E_C11.1, E_R23.2
/E_rail_disconnect/P12_OV_OK: E_R68.1, E_R69.2, E_U9.14, E_U36.6
/E_rail_disconnect/P12_OV_OK_SCHMITT: E_U11.5, E_U36.2
/E_rail_disconnect/P12_OV_REF: E_R67.2, E_R68.2, E_U9.9
/E_rail_disconnect/P12_OV_SENSE: E_C31.1, E_R65.2, E_R66.1, E_U9.8
/E_rail_disconnect/P12_TT: E_R19.1, E_U3.2
/E_rail_disconnect/P19_ALLOW: E_R4.2, E_R5.1, E_U1.3
/E_rail_disconnect/P19_COMMON: E_Q1.1, E_Q2.1, E_R2.2, E_U1.5
/E_rail_disconnect/P19_DRIVE: E_R1.1, E_U1.8
/E_rail_disconnect/P19_GATE: E_Q1.2, E_Q2.2, E_R1.2, E_R2.1
/E_rail_disconnect/P19_MCAP1: E_C2.2, E_U1.7
/E_rail_disconnect/P19_MCAP1_LIMIT: E_C2.1, E_R6.2
/E_rail_disconnect/P19_MCAP2: E_C3.2, E_U1.6
/E_rail_disconnect/P19_MCAP2_LIMIT: E_C3.1, E_R7.2
/E_rail_disconnect/P19_OV_OK: E_R60.1, E_R61.2, E_U9.2, E_U36.1
/E_rail_disconnect/P19_OV_OK_SCHMITT: E_U11.2, E_U36.7
/E_rail_disconnect/P19_OV_REF: E_R59.2, E_R60.2, E_U9.5
/E_rail_disconnect/P19_OV_SENSE: E_C30.1, E_R57.2, E_R58.1, E_U9.4
/E_rail_disconnect/P19_SENSE_MID: E_R56.2, E_R57.1
/E_rail_disconnect/P19_TT: E_R3.1, E_U1.2
/E_rail_disconnect/POS_OUTPUT_READY: E_U25.4, E_U27.3
/E_rail_disconnect/REF_HIGH_AUX: E_R88.2, E_R89.1, E_R90.1
/E_rail_disconnect/REF_HIGH_OK: E_R91.1, E_R92.2, E_U10.13, E_U38.3
/E_rail_disconnect/REF_HIGH_OK_SCHMITT: E_U11.13, E_U38.5
/E_rail_disconnect/REF_HIGH_POSITIVE: E_R90.2, E_R91.2, E_U10.11
/E_rail_disconnect/REF_LOW_AUX: E_R83.2, E_R84.1, E_U10.8
/E_rail_disconnect/REF_LOW_OK: E_R86.1, E_R87.2, E_U10.14, E_U38.1
/E_rail_disconnect/REF_LOW_OK_SCHMITT: E_U11.12, E_U38.7
/E_rail_disconnect/REF_LOW_POSITIVE: E_R85.2, E_R86.2, E_U10.9
/E_rail_disconnect/RUN_BUFFERED: E_U28.1, E_U43.4
/E_rail_disconnect/V5_REG_OV_OK: E_R76.1, E_R77.2, E_U10.2, E_U37.3
/E_rail_disconnect/V5_REG_OV_OK_SCHMITT: E_U11.9, E_U37.5
/E_rail_disconnect/V5_REG_OV_REF: E_R75.2, E_R76.2, E_U10.5
/E_rail_disconnect/V5_REG_OV_SENSE: E_C32.1, E_R73.2, E_R74.1, E_U10.4
/F_fan_health_protection/FAN_L_5V: F_C203.1, F_J202.2, F_R202.1, F_R203.1, F_U201.6
/F_fan_health_protection/FAN_L_ILIM: F_R201.1, F_U201.5
/F_fan_health_protection/FAN_L_TACH: F_J202.3, F_R14.1, F_R202.2, F_U3.1
/F_fan_health_protection/FAN_R_5V: F_C303.1, F_J203.2, F_R302.1, F_R303.1, F_U301.6
/F_fan_health_protection/FAN_R_ILIM: F_R301.1, F_U301.5
/F_fan_health_protection/FAN_R_TACH: F_J203.3, F_R15.1, F_R302.2, F_U3.3
/F_fan_health_protection/FAULT_CLK: F_U7.4, F_U8.1
/F_fan_health_protection/HEALTH_AND_WD: F_U12.4, F_U13.1
/F_fan_health_protection/HEARTBEAT: F_R4.1, F_U1.11, F_U16.2
/F_fan_health_protection/HEARTBEAT_FAST: F_U4.6, F_U16.4
/F_fan_health_protection/HW_NOFAULT: F_U11.4, F_U13.2
/F_fan_health_protection/HW_NOFAULT_5: F_R9.1, F_U8.3, F_U11.2
/F_fan_health_protection/ISP_MISO: F_J5.1, F_U1.8
/F_fan_health_protection/ISP_MOSI: F_J5.4, F_U1.7
/F_fan_health_protection/ISP_SCK: F_J5.3, F_U1.9
/F_fan_health_protection/LDO_DELAY: F_C3.1, F_U2.7
/F_fan_health_protection/LEAF_PERMISSION: F_R13.1, F_U13.4, F_U14.2
/F_fan_health_protection/LED_A: F_R1.2, F_R2.1, F_U15.1
/F_fan_health_protection/LED_K: F_R2.2, F_U14.4, F_U15.3
/F_fan_health_protection/MCU_HEALTH: F_R3.1, F_U1.6, F_U12.1
/F_fan_health_protection/MCU_RESET_N: F_J5.5, F_R6.2, F_U1.4
/F_fan_health_protection/MCU_TACH_L: F_R16.2, F_U1.10
/F_fan_health_protection/MCU_TACH_R: F_R17.2, F_U1.5
/F_fan_health_protection/NF_RAW5_ILIM: F_R401.1, F_U401.5
/F_fan_health_protection/RAW_CLEAR_FAST: F_U8.6, F_U10.4
/F_fan_health_protection/RAW_CLEAR_N: F_R10.2, F_U9.6, F_U10.2
/F_fan_health_protection/RAW_POR_CT: F_C14.1, F_U9.5
/F_fan_health_protection/RAW_POR_SENSE: F_R11.2, F_R12.1, F_U9.1
/F_fan_health_protection/TACH_L_BUF: F_R16.1, F_U3.6
/F_fan_health_protection/TACH_R_BUF: F_R17.1, F_U3.4
/F_fan_health_protection/TEMP_L_ADC: F_C22.1, F_R21.2, F_U1.13
/F_fan_health_protection/TEMP_L_NODE: F_J2.1, F_R20.2, F_R21.1
/F_fan_health_protection/TEMP_R_ADC: F_C23.1, F_R23.2, F_U1.12
/F_fan_health_protection/TEMP_R_NODE: F_J3.1, F_R22.2, F_R23.1
/F_fan_health_protection/V3V3: F_C2.1, F_C4.1, F_C5.1, F_C6.1, F_C8.1, F_C9.1, F_C16.1, F_C17.1, F_C18.1, F_C19.1, F_C24.1, F_J5.2, F_R5.1, F_R6.1, F_R7.1, F_R20.1, F_R22.1, F_R24.1, F_U1.1, F_U2.1, F_U3.5, F_U4.1, F_U4.5, F_U5.5, F_U6.1, F_U6.5, F_U11.5, F_U12.5, F_U13.5, F_U14.5, F_U16.5
/F_fan_health_protection/WD_CWD: F_C7.1, F_U4.2
/F_fan_health_protection/WD_EN: F_R7.2, F_U4.3
/F_fan_health_protection/WD_OK: F_R5.2, F_U2.3, F_U4.7, F_U4.8, F_U5.2
/F_fan_health_protection/WD_OK_5: F_R8.1, F_U6.4, F_U7.2
/F_fan_health_protection/WD_OK_FAST: F_U5.4, F_U6.3, F_U12.2
/F_fan_health_protection/XTAL1: F_C20.1, F_U1.2, F_X1.1
/F_fan_health_protection/XTAL2: F_C21.1, F_U1.3, F_X1.2
/G_module_input/MODULE_DVDT: G_C3.1, G_C4.1, G_U1.20
/G_module_input/MODULE_ILM: G_R5.1, G_U1.19
/G_module_input/MODULE_OV: G_R3.2, G_R4.1, G_U1.12
/G_module_input/MODULE_RTN: G_C3.2, G_C4.2, G_R2.2, G_R4.2, G_R5.2, G_U1.15, G_U1.25
/G_module_input/MODULE_UV: G_R1.2, G_R2.1, G_U1.10
/I_input_protection/DC_JACK: I_F1.1, I_J1.1
/M_rail_monitor/5V_DIG_OV_OK: M_R100.1, M_R101.2, M_U4.13, M_U10.13
/M_rail_monitor/5V_DIG_OV_REF: M_C32.1, M_R99.2, M_R100.2, M_U4.11
/M_rail_monitor/5V_DIG_OV_REF_BASE: M_R97.2, M_R98.1, M_R99.1
/M_rail_monitor/5V_DIG_OV_SENSE: M_C31.1, M_R95.2, M_R96.1, M_U4.10
/M_rail_monitor/5V_DIG_UV_OK: M_R93.1, M_R94.2, M_U4.14, M_U10.12
/M_rail_monitor/5V_DIG_UV_REF: M_C30.1, M_R91.2, M_R92.1, M_U4.8
/M_rail_monitor/5V_DIG_UV_RT_MID: M_R88.2, M_R89.1
/M_rail_monitor/5V_DIG_UV_SENSE: M_C29.1, M_R89.2, M_R90.1, M_R93.2, M_U4.9
/M_rail_monitor/5V_DIG_WINDOW_OK: M_U10.11, M_U11.13
/M_rail_monitor/ANALOG_WINDOWS_OK: M_U12.3, M_U12.9
/M_rail_monitor/BIAS_OK: M_U11.8, M_U12.4
/M_rail_monitor/FIVES_OK: M_U11.11, M_U12.5
/M_rail_monitor/HV_OK: M_U11.3, M_U12.1
/M_rail_monitor/LOCAL_RAIL_OK: M_R113.2, M_U7.1, M_U8.1, M_U12.13
/M_rail_monitor/LOWV_WINDOWS_OK: M_U12.6, M_U12.10
/M_rail_monitor/LV_OK: M_U11.6, M_U12.2
/M_rail_monitor/N12_FB: M_C34.2, M_R104.2, M_R105.2, M_U5.6
/M_rail_monitor/N12_INV: M_C34.1, M_R39.1, M_R44.1, M_R105.1, M_U5.7
/M_rail_monitor/N12_OV_OK: M_R49.1, M_R50.2, M_U2.13, M_U9.13
/M_rail_monitor/N12_OV_REF: M_C16.1, M_R48.2, M_R49.2, M_U2.11
/M_rail_monitor/N12_OV_REF_BASE: M_R46.2, M_R47.1, M_R48.1
/M_rail_monitor/N12_OV_REF_MID: M_R45.2, M_R46.1
/M_rail_monitor/N12_OV_SENSE: M_C15.1, M_R44.2, M_U2.10
/M_rail_monitor/N12_UV_OK: M_R42.1, M_R43.2, M_U2.14, M_U9.12
/M_rail_monitor/N12_UV_REF: M_C14.1, M_R40.2, M_R41.1, M_U2.8
/M_rail_monitor/N12_UV_SENSE: M_C13.1, M_R39.2, M_R42.2, M_U2.9
/M_rail_monitor/N12_WINDOW_OK: M_U9.11, M_U11.5
/M_rail_monitor/N19_FB: M_C33.2, M_R102.2, M_R103.2, M_U5.2
/M_rail_monitor/N19_INV: M_C33.1, M_R14.1, M_R19.1, M_R103.1, M_U5.1
/M_rail_monitor/N19_OV_OK: M_R23.1, M_R24.2, M_U1.13, M_U9.5
/M_rail_monitor/N19_OV_REF: M_C8.1, M_R22.2, M_R23.2, M_U1.11
/M_rail_monitor/N19_OV_REF_BASE: M_R20.2, M_R21.1, M_R22.1
/M_rail_monitor/N19_OV_SENSE: M_C7.1, M_R19.2, M_U1.10
/M_rail_monitor/N19_UV_OK: M_R17.1, M_R18.2, M_U1.14, M_U9.4
/M_rail_monitor/N19_UV_REF: M_C6.1, M_R15.2, M_R16.1, M_U1.8
/M_rail_monitor/N19_UV_SENSE: M_C5.1, M_R14.2, M_R17.2, M_U1.9
/M_rail_monitor/N19_WINDOW_OK: M_U9.6, M_U11.2
/M_rail_monitor/NBIAS_L: M_J3.2, M_R106.1
/M_rail_monitor/NBIAS_L_FB: M_C35.2, M_R106.2, M_R107.2, M_U5.9
/M_rail_monitor/NBIAS_L_INV: M_C35.1, M_R51.1, M_R56.1, M_R107.1, M_U5.8
/M_rail_monitor/NBIAS_L_OV_OK: M_R60.1, M_R61.2, M_U3.1, M_U10.2
/M_rail_monitor/NBIAS_L_OV_REF: M_C20.1, M_R59.2, M_R60.2, M_U3.7
/M_rail_monitor/NBIAS_L_OV_REF_BASE: M_R57.2, M_R58.1, M_R59.1
/M_rail_monitor/NBIAS_L_OV_SENSE: M_C19.1, M_R56.2, M_U3.6
/M_rail_monitor/NBIAS_L_UV_OK: M_R54.1, M_R55.2, M_U3.2, M_U10.1
/M_rail_monitor/NBIAS_L_UV_REF: M_C18.1, M_R52.2, M_R53.1, M_U3.4
/M_rail_monitor/NBIAS_L_UV_SENSE: M_C17.1, M_R51.2, M_R54.2, M_U3.5
/M_rail_monitor/NBIAS_L_WINDOW_OK: M_U10.3, M_U11.9
/M_rail_monitor/NBIAS_R: M_J3.3, M_R108.1
/M_rail_monitor/NBIAS_R_FB: M_C36.2, M_R108.2, M_R109.2, M_U5.13
/M_rail_monitor/NBIAS_R_INV: M_C36.1, M_R62.1, M_R67.1, M_R109.1, M_U5.14
/M_rail_monitor/NBIAS_R_OV_OK: M_R71.1, M_R72.2, M_U3.13, M_U10.5
/M_rail_monitor/NBIAS_R_OV_REF: M_C24.1, M_R70.2, M_R71.2, M_U3.11
/M_rail_monitor/NBIAS_R_OV_REF_BASE: M_R68.2, M_R69.1, M_R70.1
/M_rail_monitor/NBIAS_R_OV_SENSE: M_C23.1, M_R67.2, M_U3.10
/M_rail_monitor/NBIAS_R_UV_OK: M_R65.1, M_R66.2, M_U3.14, M_U10.4
/M_rail_monitor/NBIAS_R_UV_REF: M_C22.1, M_R63.2, M_R64.1, M_U3.8
/M_rail_monitor/NBIAS_R_UV_SENSE: M_C21.1, M_R62.2, M_R65.2, M_U3.9
/M_rail_monitor/NBIAS_R_WINDOW_OK: M_U10.6, M_U11.10
/M_rail_monitor/P12_OV_OK: M_R37.1, M_R38.2, M_U2.1, M_U9.10
/M_rail_monitor/P12_OV_REF: M_C12.1, M_R36.2, M_R37.2, M_U2.7
/M_rail_monitor/P12_OV_REF_BASE: M_R34.2, M_R35.1, M_R36.1
/M_rail_monitor/P12_OV_REF_MID: M_R33.2, M_R34.1
/M_rail_monitor/P12_OV_SENSE: M_C11.1, M_R31.2, M_R32.1, M_U2.6
/M_rail_monitor/P12_UV_OK: M_R29.1, M_R30.2, M_U2.2, M_U9.9
/M_rail_monitor/P12_UV_REF: M_C10.1, M_R27.2, M_R28.1, M_U2.4
/M_rail_monitor/P12_UV_SENSE: M_C9.1, M_R25.2, M_R26.1, M_R29.2, M_U2.5
/M_rail_monitor/P12_WINDOW_OK: M_U9.8, M_U11.4
/M_rail_monitor/P19_OV_OK: M_R12.1, M_R13.2, M_U1.1, M_U9.2
/M_rail_monitor/P19_OV_REF: M_C4.1, M_R11.2, M_R12.2, M_U1.7
/M_rail_monitor/P19_OV_REF_BASE: M_R9.2, M_R10.1, M_R11.1
/M_rail_monitor/P19_OV_SENSE: M_C3.1, M_R7.2, M_R8.1, M_U1.6
/M_rail_monitor/P19_UV_OK: M_R5.1, M_R6.2, M_U1.2, M_U9.1
/M_rail_monitor/P19_UV_REF: M_C2.1, M_R3.2, M_R4.1, M_U1.4
/M_rail_monitor/P19_UV_SENSE: M_C1.1, M_R1.2, M_R2.1, M_R5.2, M_U1.5
/M_rail_monitor/P19_WINDOW_OK: M_U9.3, M_U11.1
/M_rail_monitor/PRE_ANALOG_OK: M_J4.2, M_R114.1, M_U12.11
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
